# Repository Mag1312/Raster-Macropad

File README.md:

Hello!
This is Mag and I created this Raster Macropad!

========
- Raster is a macropad having a layout of 4x3, a rotary encoder and an Oled Screen.

Lets go through the Screenshots of Raster to get a better understanding it (also to get authorised by blueprint!)

Firstly the screenshot of the schematic of Raster Macropad 

Then next comes the PCB

Now comes the case!

And finally the full image!

And those are all the images!

Now time for all the componenets used!

BOM - 1. Seeed XIAO RP 2040
      2. 1N4148 Diodes
      3. MX-style switches (cherry)
      4. EC11 Rotary encoder
      5. 0.91 inch OLED display - SSD 1306 - 
      6. Blank DSA keycaps
      7. M3x16mm screws
      8. M3x5mx4mm screws
      9. 3D printed Case

Thats everything!

If you cant access the screenshots, I've included all the screenshots in the attributes folder!

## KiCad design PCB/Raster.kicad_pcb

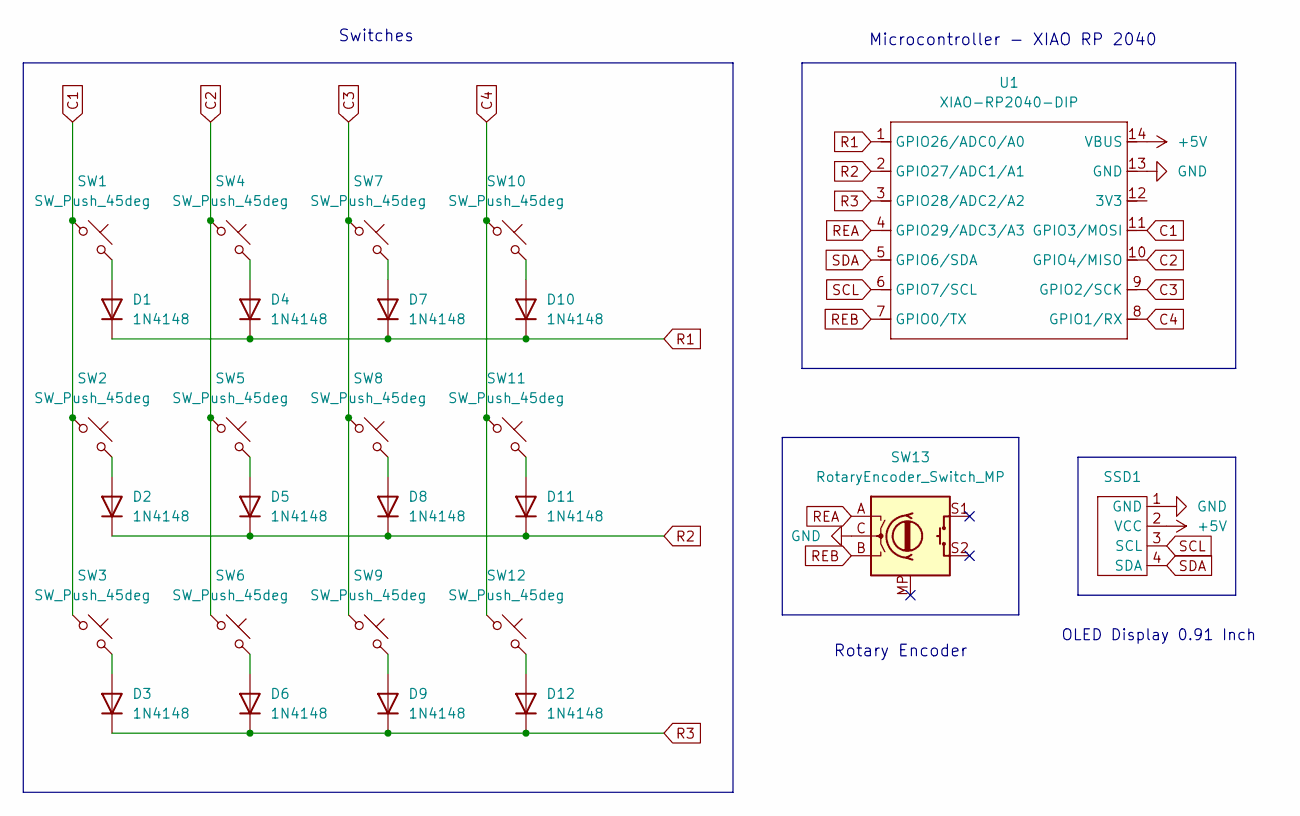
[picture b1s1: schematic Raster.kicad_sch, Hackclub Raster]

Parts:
D1, D2, D3, D4, D5, D6, D7, D8, D9, D10, D11, D12: 1N4148; D_DO-35_SOD27_P7.62mm_Horizontal
SSD1: SSD1306-0.91-OLED-4pin-128x32
SW1, SW2, SW3, SW4, SW5, SW6, SW7, SW8, SW9, SW10, SW11, SW12: SW_Push_45deg; SW_Cherry_MX_1.00u_PCB
SW13: RotaryEncoder_Switch_MP; RotaryEncoder_Alps_EC11E-Switch_Vertical_H20mm
U1: XIAO-RP2040-DIP

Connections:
+5V: SSD1.2 (VCC), U1.14 (VBUS)
C1: SW1.1, SW2.1, SW3.1, U1.11 (GPIO3/MOSI)
C2: SW4.1, SW5.1, SW6.1, U1.10 (GPIO4/MISO)
C3: SW7.1, SW8.1, SW9.1, U1.9 (GPIO2/SCK)
C4: SW10.1, SW11.1, SW12.1, U1.8 (GPIO1/RX)
GND: SSD1.1 (GND), SW13.C, U1.13 (GND)
unnamed: D1.2 (A), SW1.2
unnamed: D2.2 (A), SW2.2
unnamed: D3.2 (A), SW3.2
unnamed: D4.2 (A), SW4.2
unnamed: D5.2 (A), SW5.2
unnamed: D6.2 (A), SW6.2
unnamed: D7.2 (A), SW7.2
unnamed: D8.2 (A), SW8.2
unnamed: D9.2 (A), SW9.2
unnamed: D10.2 (A), SW10.2
unnamed: D11.2 (A), SW11.2
unnamed: D12.2 (A), SW12.2
R1: D1.1 (K), D4.1 (K), D7.1 (K), D10.1 (K), U1.1 (GPIO26/ADC0/A0)
R2: D2.1 (K), D5.1 (K), D8.1 (K), D11.1 (K), U1.2 (GPIO27/ADC1/A1)
R3: D3.1 (K), D6.1 (K), D9.1 (K), D12.1 (K), U1.3 (GPIO28/ADC2/A2)
REA: SW13.A, U1.4 (GPIO29/ADC3/A3)
REB: SW13.B, U1.7 (GPIO0/TX)
SCL: SSD1.3 (SCL), U1.6 (GPIO7/SCL)
SDA: SSD1.4 (SDA), U1.5 (GPIO6/SDA)

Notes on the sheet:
Switches
OLED Display 0.91 Inch
Microcontroller - XIAO RP 2040
Rotary Encoder

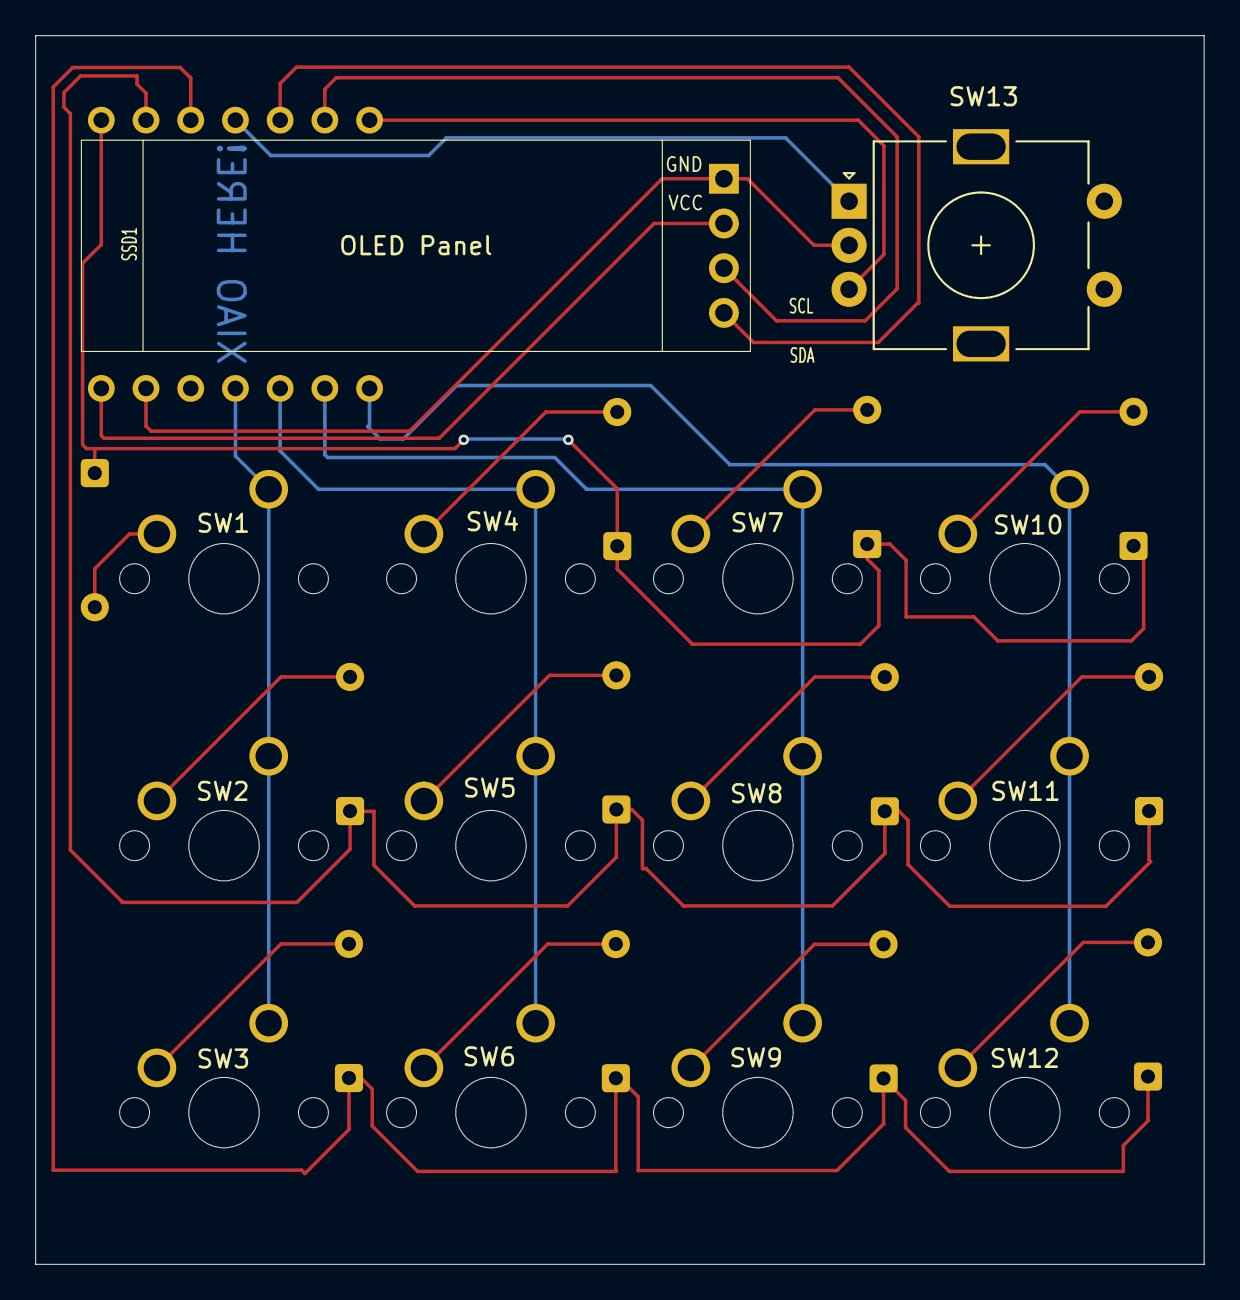
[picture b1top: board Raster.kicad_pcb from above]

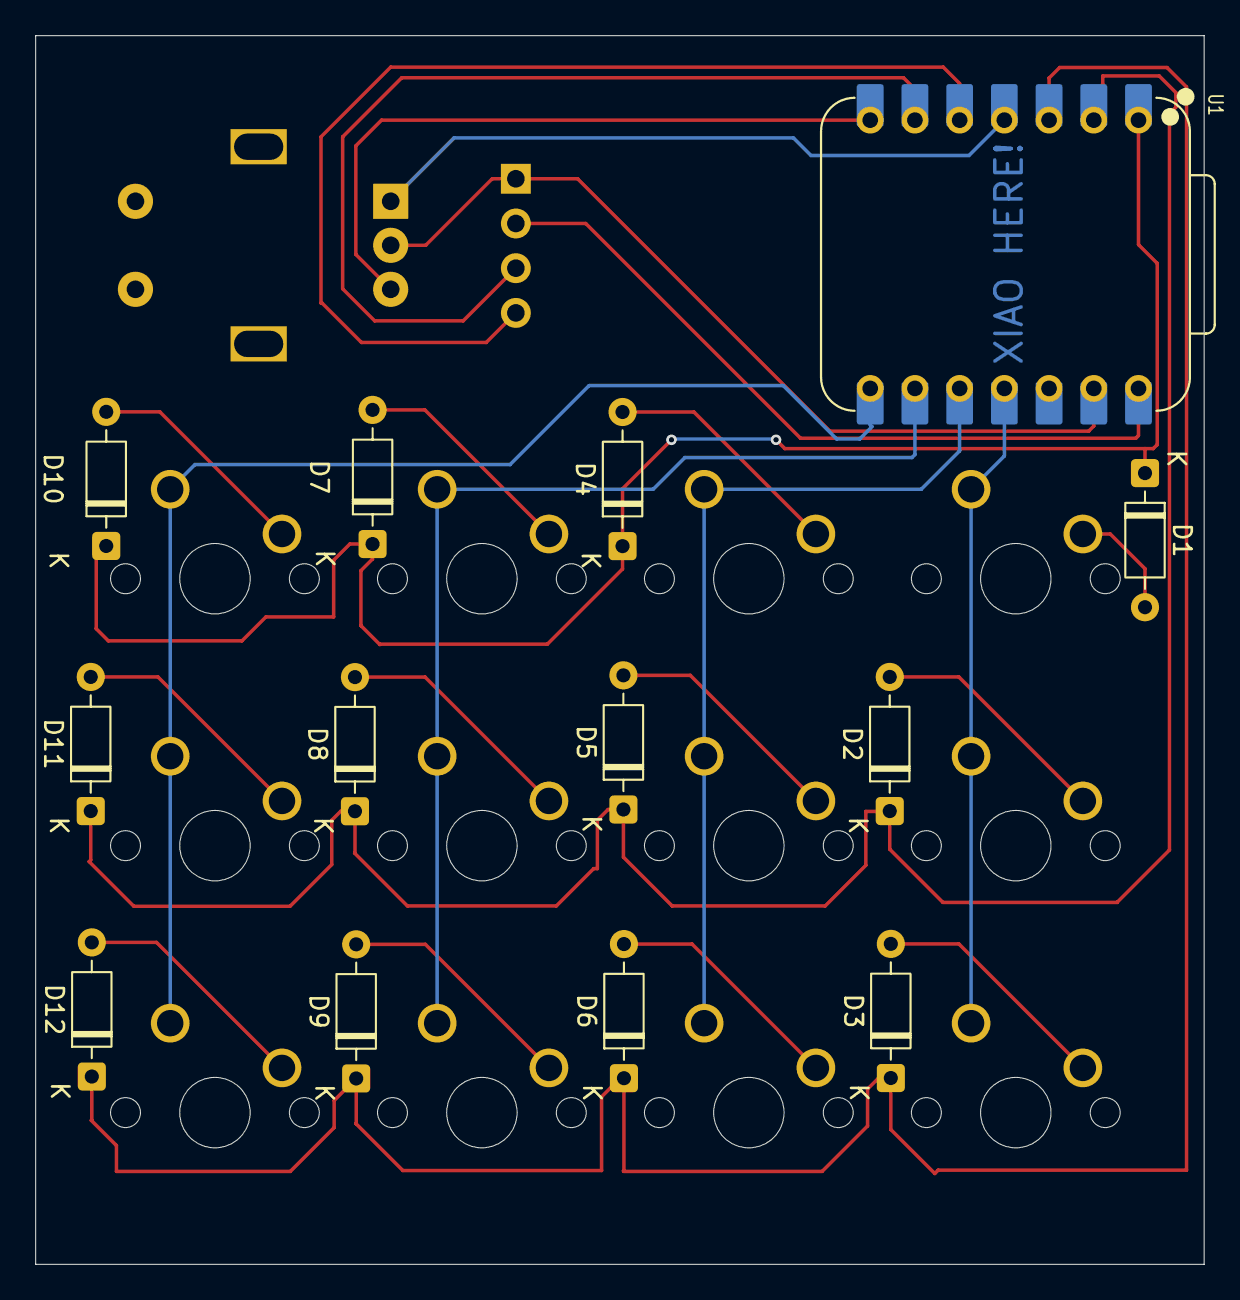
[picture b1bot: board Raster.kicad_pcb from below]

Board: 2 copper layers, 66.4 x 69.8 mm, 27 parts (13 on the bottom side), 25 nets.

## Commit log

2025-12-28 Second commit
2025-12-28 Third Commit
2025-12-29 fourth commit
2025-12-29 fifth commit
2026-04-09 YAYAYAY
